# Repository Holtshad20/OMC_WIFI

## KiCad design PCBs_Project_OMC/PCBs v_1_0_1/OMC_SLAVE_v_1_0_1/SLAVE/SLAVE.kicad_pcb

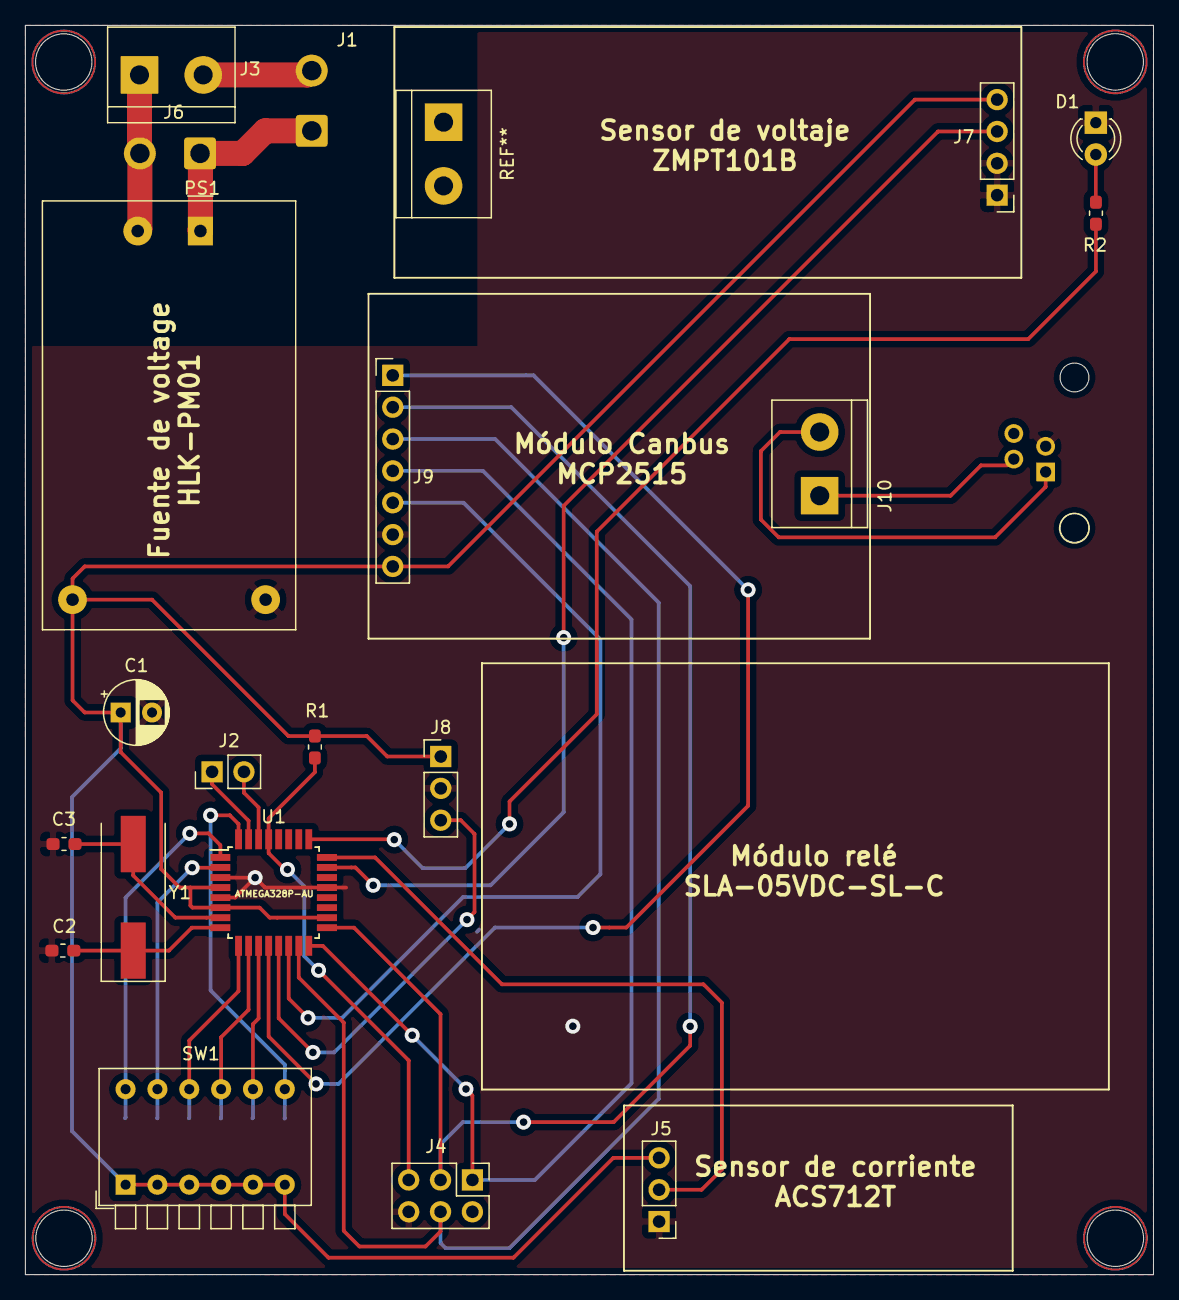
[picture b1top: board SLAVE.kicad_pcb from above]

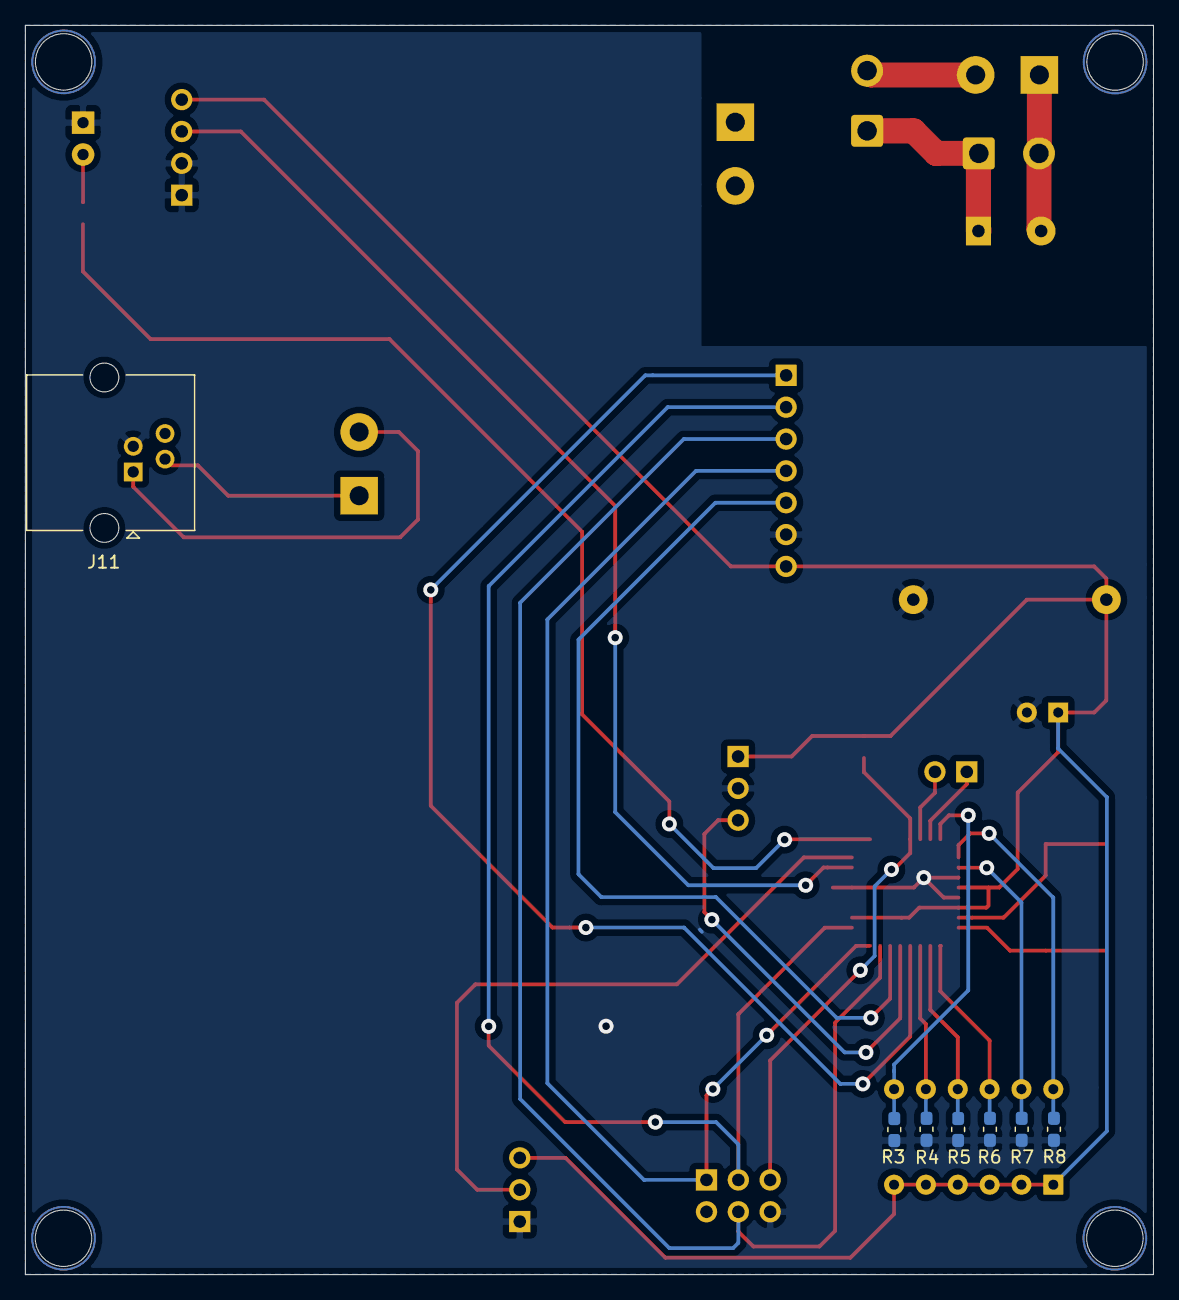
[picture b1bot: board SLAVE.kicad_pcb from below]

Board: 2 copper layers, 90.0 x 99.6 mm, 27 parts (7 on the bottom side), 28 nets.

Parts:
C1: 0.1uf; CP_Radial_D5.0mm_P2.50mm
C2, C3: 22pF; C_0603_1608Metric_Pad1.05x0.95mm_HandSolder
D1: LED; LED_D3.0mm
J1: SW; SolderWire-0.75sqmm_1x02_P4.8mm_D1.25mm_OD2.3mm
J2: UART; PinHeader_1x02_P2.54mm_Vertical
J3: Screw_Terminal_01x02; TerminalBlock_bornier-2_P5.08mm
J4: ICSP; PinHeader_2x03_P2.54mm_Vertical
J5: Conn_01x03_Female_SI; PinHeader_1x03_P2.54mm_Vertical
J6: Conn_01x02_Female_SV; SolderWire-0.75sqmm_1x02_P4.8mm_D1.25mm_OD2.3mm
J7: Conn_01x04_Female_SV; PinHeader_1x04_P2.54mm_Vertical
J8: Conn_01x03_Female_Rele; PinHeader_1x03_P2.54mm_Vertical
J9: Conn_01x07_Female_CanBus; PinHeader_1x07_P2.54mm_Vertical
J10: Conn_01x02_Female_CanBus; TerminalBlock_bornier-2_P5.08mm
J11: RJ14; RJ14_Connfly_DS1133-S4_Horizontal
PS1: HLK-PM01/5M05; Converter_ACDC_HiLink_HLK-PMxx
R1, R3, R4, R5, R6, R7, R8: 10k; R_0603_1608Metric_Pad1.05x0.95mm_HandSolder
R2: 330; R_0603_1608Metric_Pad1.05x0.95mm_HandSolder
SW1: SW_DIP_x06; SW_DIP_SPSTx06_Piano_10.8x16.8mm_W7.62mm_P2.54mm
U1: ATmega328P-MU; TQFP-32_7x7mm_P0.8mm
Y1: Crystal; Crystal_SMD_HC49-SD

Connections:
+5V: C1.1, J5.3, J7.4, J8.1, J9.7, PS1.4, R1.1, SW1.1, SW1.2, SW1.3, SW1.4, SW1.5, SW1.6, U1.4, U1.6, U1.18
/H: J10.2, J11.1
/L: J10.1, J11.2
CS: J9.5, U1.14
GND: C1.2, C2.2, C3.2, D1.1, J4.6, J5.1, J7.1, J7.2, J8.2, J9.6, J11.3, PS1.3, R3.1, R4.1, R5.1, R6.1, R7.1, R8.1, U1.3, U1.5, U1.21
INTERRUPT: J9.1, U1.12
I_Sensor: J5.2, U1.24
MISO: J4.1, J9.4, U1.16
MOSI: J4.4, J9.3, U1.15
unnamed: D1.2, R2.2
unnamed: J1.1, J6.1, PS1.1
unnamed: J1.2, J3.2
unnamed: J3.1, J6.2, PS1.2
unnamed: R2.1, U1.25
unnamed: R3.2, SW1.7, U1.32
unnamed: R4.2, SW1.8, U1.11
unnamed: R5.2, SW1.9, U1.10
unnamed: R6.2, SW1.10, U1.9
unnamed: R7.2, SW1.11, U1.2
unnamed: R8.2, SW1.12, U1.1
RELAY: J8.3, U1.13
RESET: J4.5, R1.2, U1.29
RX: J2.2, U1.30
SCK: J4.3, J9.2, U1.17
TX: J2.1, U1.31
V_Sensor: J7.3, U1.23
XTAL1: C3.1, U1.7, Y1.2
XTAL2: C2.1, U1.8, Y1.1
